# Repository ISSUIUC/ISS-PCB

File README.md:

# Welcome to the ISS-PCB repo! 🖥️⚙️⚡

# Repository Overview

* Boards: Contains all of the present boards the team is working on
    - Moved Board Archive to the [Archive](https://github.com/ISSUIUC/ISS-PCB-Archive) repo... check it out! 😁
* Docs: Contains various documents pertaining to PCB designs
* Libs: Contains various templates, symbols and footprints that we use when designing PCBs
* Scripts: Contains various codes used in PCB development
* Documentation & Tutorial Mark Down Files: 
    - README.md: Introduces the ISS-PCB Repo and pertinent information to become an amazing E-Hardware member
    - ISS-PCB-CONVENTIONS.md: Sets conventions to be followed when desiging for the ISS-PCB KiCad repo
    - HOW-TO.md: Presents brief and thorough lessons on important KiCad tools, documenation procedures, and design processes
    - GITHUB.md: An introduction to GitHub and how to use it for KiCad
    - CONTRIBUTING.md: Showcases how to setup KiCad and contribute proper work to E-Hardware. Additionally, introduces many conventions of ISS-PCB folder. 

When you commit changes to the repository, they will generally be found in the Boards folder. 

# E-Hardware PCB Documentation 

* You can find documentation about all of our PCBs in the [Spaceshot Members Box Folder](https://uofi.app.box.com/folder/273741222408). 
    - Alternatively, [Members] Spaceshot > Avionics > Development 

# How to contribute:
There are many ways to contribute to the PCBs that we build for the rocket and its accompanying systems. The timeline for building a PCB is usually as follows: 

* Formulate the requirements of the board
* Research different chips, understand their functionalities, and determine if we can use it for our purposes
* Build the board schematic using the datasheets of different chips 
* Route the board 
* Once the board is manufactured, solder all the components onto the board
* Debug the board 
* Document the board (this should be done throughout the process as well) 

Every part of constructing a PCB is hands-on, and there are lots of ways to get involved. 

To have your changes reflected on the board, it is important to commit your changes to the Github repository. To learn how to commit changes, check out the [Contributing Guide](/CONTRIBUTING.md).

# Useful Links:
Here are some links you may find useful as you are building PCBs: 

* [KiCad](https://www.kicad.org/) - software used for designing PCBs 

* [KiCad Library Conventions](https://klc.kicad.org/) - guidelines for creation of symbols, footprints, and 3D models in KiCad

* [DigiKey](https://www.digikey.com/) - used for looking up various electronic components

* [Mouser](https://www.mouser.com/) - used for looking up various electronic components

* [JLCPCB](https://jlcpcb.com) - the PCB manufacturer we primarily use

* [JLCPCB Design Rules](https://jlcpcb.com/capabilities/Capabilities) - the design constraints JLCPCB imposes

Thanks for reading, and good luck in building PCBs! 

*See a typo? Think we left some vital information out? Make a branch and edit this file!*

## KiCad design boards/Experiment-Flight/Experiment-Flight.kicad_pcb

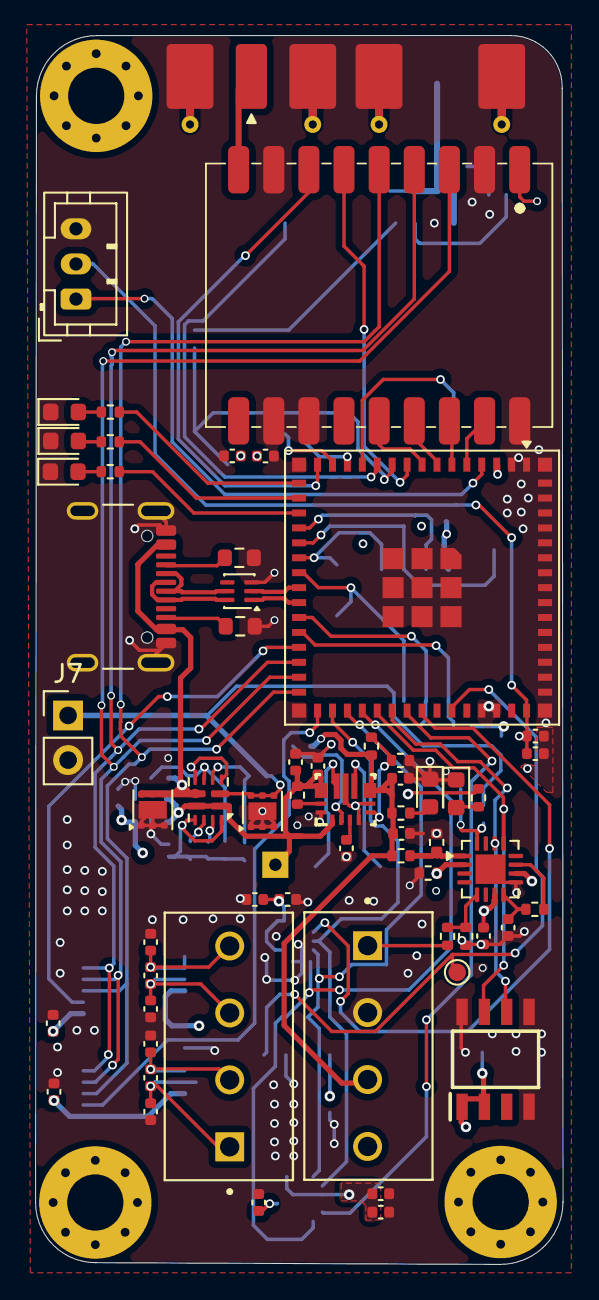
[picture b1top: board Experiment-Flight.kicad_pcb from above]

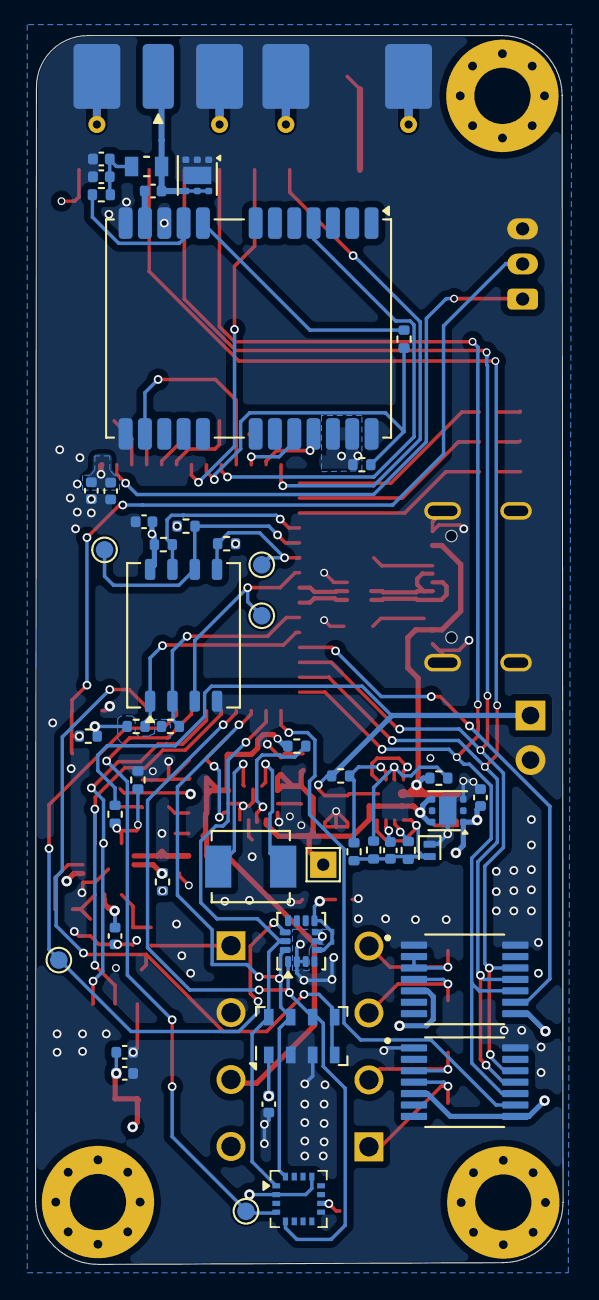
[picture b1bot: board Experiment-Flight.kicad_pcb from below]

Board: 4 copper layers, 30.0 x 70.0 mm, 113 parts (49 on the bottom side), 81 nets.

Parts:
C1, C2, C3, C5, C12, C33, C34: 1uF; C_0402_1005Metric
C6, C9, C16, C21, C23, C27: 0.1uF; C_0402_1005Metric
C8, C10: 47pF; C_0402_1005Metric
C13, C14, C18, C20, C25, C26, C28, C29, C32, C105: 100nF; C_0402_1005Metric
C15, C17, C22, C24: 0.01uF; C_0402_1005Metric
C19, C30, C36: 10uF; C_0402_1005Metric
C31, C37: 47uF; C_0402_1005Metric
C35: 4.7uF; C_0402_1005Metric
C104: 22uF; C_0402_1005Metric
D1: BAS116L; D_SOD-882
D2, D106: ORANGE_LED; LED_0603_1608Metric
D3, D104: RED LED; LED_0603_1608Metric
D105: BLUE LED; LED_0603_1608Metric
H1, H2, H3: MountingHole; MountingHole_3.2mm_M3_Pad_Via
IC1: NEO-F10N-00B; ublox_NEO
J1: USB4105-GF-A; USB_C_Receptacle_GCT_USB4105-xx-A_16P_TopMnt_Horizontal
J2, J4: SMA; SMA_Molex_73251-2120_EdgeMount_Horizontal
J5: TestPoint; TestPoint_THTPad_1.5x1.5mm_Drill0.7mm
J7: JST; PinHeader_1x02_P2.54mm_Vertical
J8: Conn_01x03; JST_PH_B3B-PH-K_1x03_P2.00mm_Vertical
J10, J11: Screw_Terminal_01x04; PHOENIX_1727036
L1: 33nH; INDC1609X100N
L2: 1uH; IND_SRP4020TA-1R0M
R1, R24, R27, R104, R105, R108, R109, R110, R111: 100k; R_0402_1005Metric
R2, R3: 5.1k; R_0603_1608Metric
R4: 20k; R_0402_1005Metric
R6: 10; R_0402_1005Metric
R7: 33; R_0402_1005Metric
R8, R16, R19: 10k; R_0402_1005Metric
R10, R11, R12, R13, R14: 50k; R_0402_1005Metric
R15: 4.7k; R_0402_1005Metric
R17, R20: 16.9k; R_0402_1005Metric
R18, R21: 5k; R_0402_1005Metric
R22: 21.5k; R_0402_1005Metric
R23: 523k; R_0402_1005Metric
R25, R26, R121, R122, R123: 470; R_0402_1005Metric
TP102, TP103, TP104, TP105, TP106, TP107: TestPoint_Small; TestPoint_Pad_D1.0mm
U1: ADS7138-Q1; WQFN-16-1EP_3x3mm_P0.5mm_EP1.68x1.68mm
U2: ESP32-S3-MINI-1U; ESP32-S2-MINI-1U
U3: ECMF02-2AMX6; ST_UQFN-6L_1.5x1.7mm_P0.5mm
U4, U13, U14: TVS1800DRV; WSON-6-1EP_2x2mm_P0.65mm_EP1x1.6mm
U5: LR2021
U6: ZDSD64GLGEAG-R; LGA-8_8x6.2mm_P1.27mm
U7: MMC5983MA; LGA-16_3x3mm_P0.5mm
U8, U9: MAX31856MUD_T; MAX31856
U10: LSM6DSV320X; LGA-14_3x2.5mm_P0.5mm_LayoutBorder3x4y
U11: MS5611-01BA; LGA-8_3x5mm_P1.25mm
U12: AS5600-ASOM; SOIC127P600X175-8N
U15: TPS63070; RNM0015A
U16: TPS2121; Texas_VQFN-HR-12_2x2.5mm_P0.5mm
U17: TPS746-Q1; WSON-6-1EP_2x2mm_P0.65mm_EP1x1.6mm

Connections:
+3V3: C2.1, C3.1, C12.1, C13.1, C14.2, C18.1, C20.1, C21.1, C25.1, C26.1, C27.1, C28.1, C29.1, C30.1, C35.1, C104.1, C105.1, IC1.22 (V_BCKP), IC1.23 (VCC), R4.1, R8.1, R10.2, R11.2, R12.2, R13.2, R14.2, R26.1, R110.1, U1.7 (AVDD), U1.10 (DVDD), U2.3 (3V3), U5.1 (VCC), U6.8 (VDD), U7.2 (VDD), U7.13 (VDDIO), U8.5 (AVDD), U8.8 (DVDD), U9.5 (AVDD), U9.8 (DVDD), U10.5 (VDDIO), U10.8 (VDD), U11.1 (VDD), U12.1 (VDD5V), U12.2 (VDD3V3), U17.1 (OUT)
/3V3_SENSE: R110.2, R111.1, U1.2 (AIN3/GPIO3)
/5V: C36.1, C37.1, J11.3, R23.1, R25.1, R27.1, R108.1, U15.7 (VOUT), U15.8 (VOUT)
/5V_SENSE: R108.2, R109.1, U1.1 (ANI2/GPIO2)
/BOOT_SW: J8.1, U2.4 (IO0)
/B_UART_RX: IC1.20 (TXD), U2.13 (IO9)
/B_UART_TX: IC1.21 (RXD), U2.14 (IO10)
/D+: J1.A6 (D+), J1.B6 (D+), U3.6 (D+_out)
/D-: J1.A7 (D-), J1.B7 (D-), U3.5 (D-_out)
/EN: C5.2, C9.1, J8.2, R4.2, U2.45 (EN)
/FLASH_CLK: TP106.1 (1_1), U2.22 (IO18), U6.3 (CLK)
/FLASH_CMD: R14.1, TP105.1 (1_1), U2.21 (IO17), U6.5 (CMD)
/FLASH_DAT0: R10.1, TP107.1 (1_1), U2.20 (IO16), U6.6 (DAT0)
/FLASH_DAT1: R11.1, U2.19 (IO15), U6.7 (DAT1)
/FLASH_DAT2: R12.1, U2.26 (IO26), U6.1 (DAT2)
/FLASH_DAT3: R13.1, U2.25 (IO21), U6.2 (DAT3)
/GNSS_ANT: C10.1, IC1.11 (RF_IN)
/GNSS_EXT_INT: IC1.4 (EXTINT), U2.11 (IO7)
/I2C_SCL: U1.13 (SCL), U2.35 (IO39), U12.7 (SCL)
/I2C_SDA: U1.14 (SDA), U2.36 (IO40), U12.6 (SDA)
/LED_BLUE: R122.1, U2.18 (IO14)
/LED_ORANGE: R123.1, U2.17 (IO13)
/LED_RED: R121.1, U2.16 (IO12)
/LNA_EN: IC1.14 (LNA_EN), U2.12 (IO8)
/LR2021_ANT: J4.1 (In), U5.9 (ANT)
/LR2021_BUSY: U2.15 (IO11), U5.7 (BUSY)
/LR2021_CS: U2.9 (IO5), U5.6 (~CS)
/LR2021_GPIO7: U2.5 (IO1), U5.17 (DIO7)
/LR2021_GPIO8: U2.6 (IO2), U5.16 (DIO8)
/LR2021_GPIO9: U2.7 (IO3), U5.15 (DIO9)
/LR2021_nRST: U2.8 (IO4), U5.14 (nRST)
/LSM_CS: TP104.1 (1_1), U2.38 (IO42), U10.12 (CS)
/MAG_CS: TP102.1 (1_1), U2.37 (IO41), U7.4 (CS)
/MAX31856_CS_1: U2.31 (IO35), U9.9 (~CS)
/MAX31856_CS_2: U2.27 (IO47), U8.9 (~CS)
/MS5611_CS: TP103.1 (1_1), U2.40 (RXD0), U11.4 (CSB), U11.5 (CSB)
/N_GNSS_RESET: R7.2, R8.2, U2.10 (IO6)
/PRESSURE+: J11.1, R15.1
/PRESSURE_SENSE: R15.2, R16.1, U1.5 (AIN6/GPIO6)
/Power/PMUX_GND: C33.1, D1.2 (A), R18.2, R21.2, R22.1, U16.3 (CP2), U16.6 (PR1), U16.9 (ST), U16.12 (GND)
/Power/SYS_POWER: C31.1, C34.1, J5.1 (Pin_1_1), R19.2, U15.1 (PS_SYNC), U15.12 (VIN), U15.13 (VIN), U16.1 (OUT), U16.8 (OUT), U17.4 (EN), U17.6 (IN)
/SPI1_MISO: U2.34 (IO38), U7.5 (SDO), U10.1 (SDO/TA0), U11.6 (SDO)
/SPI1_MOSI: U2.33 (IO37), U7.16 (SDI), U10.14 (SDA), U11.7 (SDI/SDA)
/SPI1_SCK: U2.32 (IO36), U7.1 (SCK), U10.13 (SCL), U11.8 (SCLK)
/SPI2_MISO: U2.29 (IO34), U5.3 (MISO), U8.11 (SDO), U9.11 (SDO)
/SPI2_MOSI: U2.28 (IO33), U5.4 (MOSI), U8.12 (SDI), U9.12 (SDI)
/SPI2_SCK: U2.30 (IO48), U5.5 (SCK), U8.10 (SCK), U9.10 (SCK)
/T_1+: C22.1, C23.1, J10.1, U9.4 (T+)
/T_1-: C23.2, C24.1, J10.2, U9.2 (BIAS), U9.3 (T-)
/T_2+: C15.1, C16.1, J10.3, U8.4 (T+)
/T_2-: C16.2, C17.1, J10.4, U8.2 (BIAS), U8.3 (T-)
/USB_D+: U2.24 (USB_D+), U3.1 (D+_in)
/USB_D-: U2.23 (USB_D-), U3.2 (D-_in)
/USB_POWER: J1.A4 (VBUS), J1.A9 (VBUS), J1.B4 (VBUS), J1.B9 (VBUS), R17.1, U13.4 (IN), U13.5 (IN), U13.6 (IN), U16.7 (IN1)
/VBAT: J7.1, R20.1, R104.1, U14.4 (IN), U14.5 (IN), U14.6 (IN), U16.2 (IN2)
/VBAT_SENSE: R104.2, R105.1, U1.16 (AIN1/GPIO1)
/VCC_RF: IC1.9 (VCC_RF), R6.2
GND: C1.2, C2.2, C3.2, C5.1, C6.2, C8.2, C9.2, C12.2, C13.2, C14.1, C15.2, C17.2, C18.2, C19.2, C20.2, C21.2, C22.2, C24.2, C25.2, C26.2, C27.2, C28.2, C29.2, C30.2, C31.2, C32.2, C34.2, C35.2, C36.2, C37.2, C104.2, C105.2, D1.1 (K), D2.1 (K), D3.1 (K), D104.1 (K), D105.1 (K), D106.1 (K), IC1.10 (GND_1), IC1.12 (GND_2), IC1.13 (GND_3), IC1.24 (GND_4), J1.A1 (GND), J1.A12 (GND), J1.B1 (GND), J1.B12 (GND), J1.S1 (SHIELD), J2.2 (Ext), J4.2 (Ext), J7.2, J8.3, J11.2, R2.1, R3.1, R16.2, R24.2, R105.2, R109.2, R111.2, U1.9 (GND), U1.17 (EPAD), U2.1 (GND), U2.2 (GND), U2.42 (GND), U2.43 (GND), U2.46 (GND), U2.47 (GND), U2.48 (GND), U2.49 (GND), U2.50 (GND), U2.51 (GND), U2.52 (GND), U2.53 (GND), U2.54 (GND), U2.55 (GND), U2.56 (GND), U2.57 (GND), U2.58 (GND), U2.59 (GND), U2.60 (GND), U2.61 (GND), U2.62 (GND), U2.63 (GND), U2.64 (GND), U2.65 (GND), U3.3 (GND), U4.1 (GND), U4.2 (GND), U4.3 (GND), U4.7 (GND), U5.2 (GND), U5.8 (GND), U5.11 (GND), U5.12 (GND), U5.18 (GND), U6.4 (GND), U7.9 (GND), U7.11 (GND), U8.1 (AGND), U8.14 (DGND), U9.1 (AGND), U9.14 (DGND), U10.2 (SDx), U10.3 (SCx), U10.6 (GND), U10.7 (GND), U11.2 (PS), U11.3 (GND), U12.4 (GND), U12.5 (PGO), U12.8 (DIR), U13.1 (GND), U13.2 (GND), U13.3 (GND), U13.7 (GND), U14.1 (GND), U14.2 (GND), U14.3 (GND), U14.7 (GND), U15.4 (GND), U15.6 (FB2), U15.10 (PGND), U15.15 (VSEL), U17.3 (GND), U17.7 (EP)
unnamed: C6.1, C8.1, L1.1, R6.1
unnamed: D2.2 (A), R25.2
unnamed: D3.2 (A), R26.2
unnamed: D104.2 (A), R121.2
unnamed: D105.2 (A), R122.2
unnamed: D106.2 (A), R123.2
unnamed: IC1.8 (RESET_N), R7.1
unnamed: J1.A5 (CC1), R2.2
unnamed: J1.B5 (CC2), R3.2
unnamed: C10.2, J2.1 (In), L1.2, U4.4 (IN), U4.5 (IN), U4.6 (IN)
unnamed: R1.1, U1.11 (ADDR)
unnamed: C1.1, R1.2, U1.8 (DECAP)
unnamed: C19.1, U7.10 (CAP)
unnamed: R19.1, U15.14 (EN)
unnamed: R23.2, R24.1, U15.5 (FB)
unnamed: L2.1, U15.11 (L1)
unnamed: L2.2, U15.9 (L2)
unnamed: R27.2, U15.2 (PG)
unnamed: C32.1, U15.3 (VAUX)
unnamed: R22.2, U16.10 (ILM)
unnamed: R17.2, R18.1, U16.5 (OV1)
unnamed: R20.2, R21.1, U16.4 (OV2)
unnamed: C33.2, U16.11 (SS)

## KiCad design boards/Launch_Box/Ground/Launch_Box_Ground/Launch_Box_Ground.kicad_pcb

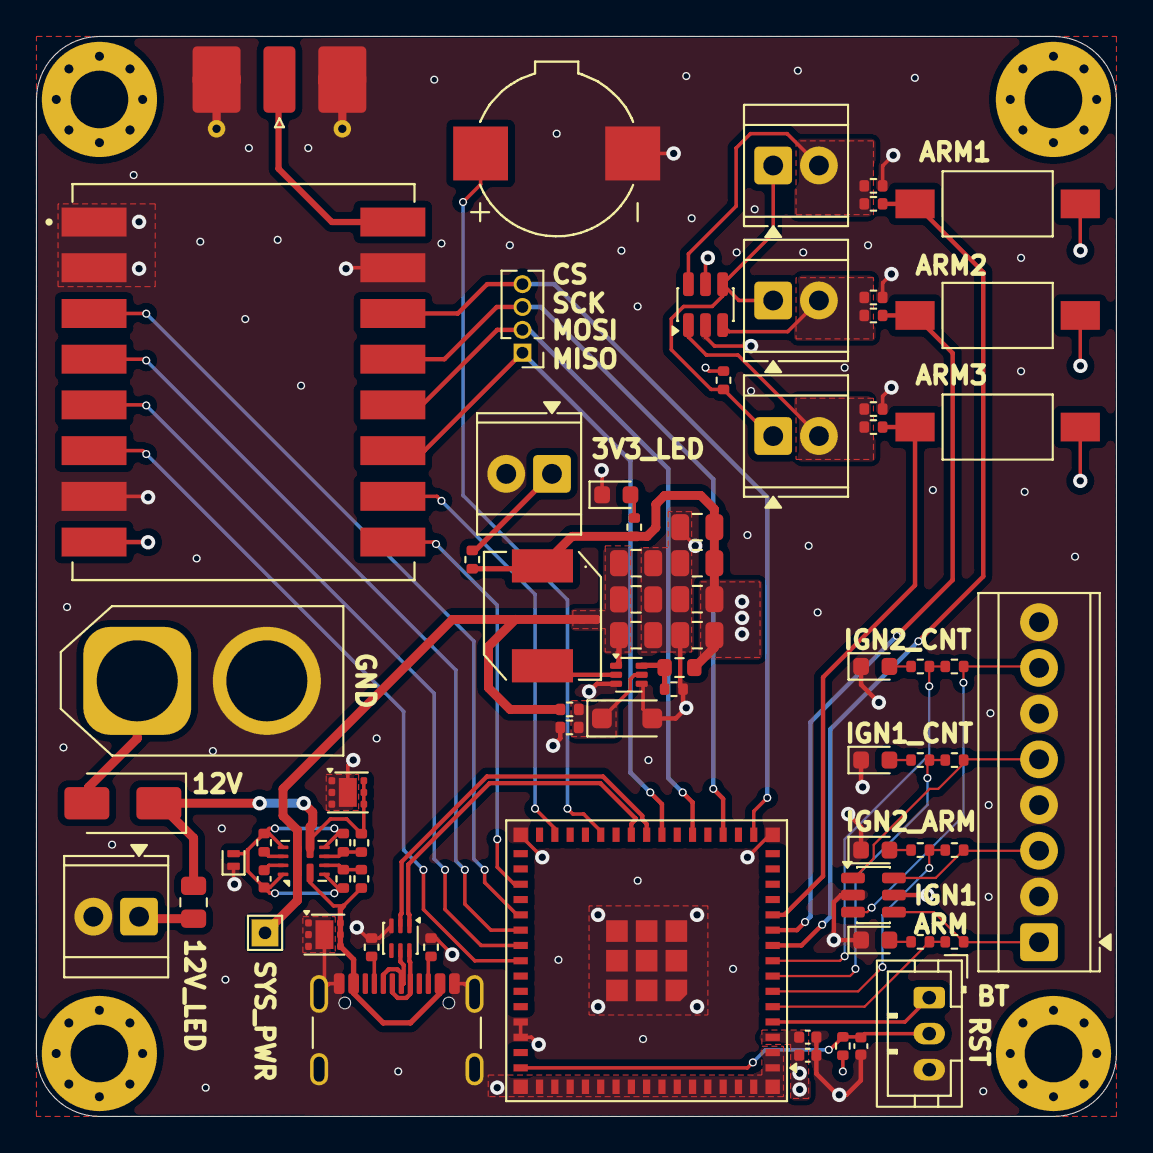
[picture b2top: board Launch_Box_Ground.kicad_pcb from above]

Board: 4 copper layers, 60.0 x 60.0 mm, 79 parts (0 on the bottom side), 56 nets.

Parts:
BZ1: Buzzer; Buzzer_SMTB-0927-TW-R
C1: 22uF; C_0402_1005Metric
C2: 100nF; C_0402_1005Metric
C3, C8: 1uF; C_0402_1005Metric
C4: 0.1uF; C_0805_2012Metric
C5, C6: 10uF; C_0805_2012Metric
C7, C9, C10, C11: 22uF; C_0805_2012Metric
D1: SS34; D_SMA
D2, D3: GREEN LED; LED_0603_1608Metric
D4, D5, D8: RED LED; LED_0603_1608Metric
D6: BZT52H-A5V1-QX; D_SOD-123F
D7: BAS116L; D_SOD-882
H1, H2, H3, H4: M3; MountingHole_3.2mm_M3_Pad_Via
J1: Conn_01x03; JST_PH_B3B-PH-K_1x03_P2.00mm_Vertical
J2: USB4105-GF-A; USB_C_Receptacle_GCT_USB4105-xx-A_16P_TopMnt_Horizontal
J3: Conn_01x04; PinHeader_1x04_P1.27mm_Vertical
J4: SMA
J5: XT60; AMASS_XT60-F_1x02_P7.20mm_Vertical
J6, J8, J9, J11, J12: Screw_Terminal_01x02; TerminalBlock_TE_282834-2_1x02_P2.54mm_Horizontal
J7: Screw_Terminal_01x08; TerminalBlock_TE_282834-8_1x08_P2.54mm_Horizontal
J10: TestPoint; TestPoint_THTPad_1.5x1.5mm_Drill0.7mm
L1: 2.2uH; L_TDK_SPM6530
R1, R21: 20k; R_0402_1005Metric
R2, R3: 5.1k; R_0402_1005Metric
R4, R5, R9, R10, R11, R12, R13, R14, R28, R30: 470; R_0402_1005Metric
R6: 100R; R_0402_1005Metric
R7, R15, R16: 1k; R_0402_1005Metric
R8, R17, R18: 10k; R_0402_1005Metric
R19: 62k; R_0402_1005Metric
R20, R24: 5k; R_0402_1005Metric
R22, R25: 30k; R_0402_1005Metric
R23: 16.9k; R_0402_1005Metric
R26: 135k; R_0603_1608Metric
R27: 80.6k; R_0402_1005Metric
R29: 2k; R_0805_2012Metric
SW1, SW2, SW3: SW_Push; SW_SPST_FSMSM
U1: ESP32-S3-MINI-1U; ESP32-S2-MINI-1U
U2: CORE1262-868M; XCVR_CORE1262-868M
U3: ECMF02-2AMX6; ST_UQFN-6L_1.5x1.7mm_P0.5mm
U4, U5: SRV05-4; SOT-23-6
U6, U7: TVS1800DRV; WSON-6-1EP_2x2mm_P0.65mm_EP1x1.6mm
U8: TI_TPS566242; SOT-563
U9: TPS2121; Texas_VQFN-HR-12_2x2.5mm_P0.5mm

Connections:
+3V3: C1.1, C2.1, C7.1, C9.1, C10.1, C11.1, L1.1, R1.2, R6.1, R26.2, R28.1, R30.1, SW1.1, SW2.1, SW3.1, U1.3 (3V3), U2.8 (3V3), U4.5 (VP), U5.5 (VP)
/12V_VBAT: D1.1 (K), R19.1, R29.1, U6.4 (IN), U6.5 (IN), U6.6 (IN), U9.7 (IN1)
/ANT_SX1262: J4.1 (In), U2.16 (ANT)
/ARMED_1: R15.1, SW1.2, U1.9 (IO5)
/ARMED_2: R16.1, SW2.2, U1.10 (IO6)
/BOOT_SW: J1.1, U1.4 (IO0)
/BUZZER: BZ1.1 (+), U1.26 (IO26)
/D+: J2.A6 (D+), J2.B6 (D+), U3.6 (D+_out)
/D-: J2.A7 (D-), J2.B7 (D-), U3.5 (D-_out)
/Ground_User_Controls/TVS_3V3_FEED: J6.1, J8.1, J9.1, R6.2, U4.4 (IO3)
/Ground_User_Controls/TVS_ARMED_1: J8.2, R15.2, R17.1, U4.6 (IO4)
/Ground_User_Controls/TVS_ARMED_2: J9.2, R16.2, R18.1, U4.3 (IO2)
/Ground_User_Controls/TVS_IGN_1_ARM: J7.1, R11.1, U5.4 (IO3)
/Ground_User_Controls/TVS_IGN_1_CNT: J7.5, R13.1, U5.1 (IO1)
/Ground_User_Controls/TVS_IGN_2_ARM: J7.3, R12.1, U5.6 (IO4)
/Ground_User_Controls/TVS_IGN_2_CNT: J7.7, R14.1, U5.3 (IO2)
/Ground_User_Controls/TVS_LAUNCH: J6.2, R7.2, R8.1, U4.1 (IO1)
/LAUNCH: R7.1, SW3.2, U1.11 (IO7)
/LED_RED_IGNITER_1_ARMED: R9.1, R11.2, U1.5 (IO1)
/LED_RED_IGNITER_1_CONTINUITY: R4.1, R13.2, U1.7 (IO3)
/LED_RED_IGNITER_2_ARMED: R10.1, R12.2, U1.6 (IO2)
/LED_RED_IGNITER_2_CONTINUITY: R5.1, R14.2, U1.8 (IO4)
/Power/PMUX_GND: C8.1, D7.2 (A), R20.2, R24.2, R27.1, U9.3 (CP2), U9.6 (PR1), U9.9 (ST), U9.12 (GND)
/Power/SYS_POWER: C4.1, C5.1, C6.1, J10.1 (Pin_1_1), R21.1, U8.1 (VIN), U9.1 (OUT), U9.8 (OUT)
/RESET_SW: C3.1, J1.2, R1.1, U1.45 (EN)
/SPI0_MISO: J3.1, U1.22 (IO18), U2.11 (MISO)
/SPI0_MOSI: J3.2, U1.20 (IO16), U2.12 (MOSI)
/SPI0_SCK: J3.3, U1.18 (IO14), U2.13 (CLK)
/SX1262_BUSY: U1.33 (IO37), U2.9 (BUSY)
/SX1262_CS: J3.4, U1.16 (IO12), U2.14 (CS)
/SX1262_GPIO_1: U1.38 (IO42), U2.6 (DIO1)
/SX1262_GPIO_2: U1.37 (IO41), U2.5 (DIO2)
/SX1262_RESET: U1.29 (IO34), U2.10 (RESET)
/SX1262_RX_EN: U1.35 (IO39), U2.3 (RXEN)
/SX1262_TX_EN: U1.36 (IO40), U2.4 (TXEN)
/USB_D+: U1.24 (USB_D+), U3.1 (D+_in)
/USB_D-: U1.23 (USB_D-), U3.2 (D-_in)
/USB_POWER: J2.A4 (VBUS), J2.A9 (VBUS), J2.B4 (VBUS), J2.B9 (VBUS), R23.1, U7.4 (IN), U7.5 (IN), U7.6 (IN), U9.2 (IN2)
GND: BZ1.2 (-), C1.2, C2.2, C3.2, C4.2, C5.2, C6.2, C7.2, C9.2, C10.2, C11.2, D2.1 (K), D3.1 (K), D4.1 (K), D5.1 (K), D6.2 (A), D7.1 (K), D8.1 (K), J1.3, J2.A1 (GND), J2.A12 (GND), J2.B1 (GND), J2.B12 (GND), J2.S1 (SHIELD), J4.2 (Ext), J5.2, J7.2, J7.4, J7.6, J7.8, J11.2, J12.2, R2.2, R3.2, R8.2, R17.2, R18.2, R22.2, R25.2, U1.1 (GND), U1.2 (GND), U1.42 (GND), U1.43 (GND), U1.46 (GND), U1.47 (GND), U1.48 (GND), U1.49 (GND), U1.50 (GND), U1.51 (GND), U1.52 (GND), U1.53 (GND), U1.54 (GND), U1.55 (GND), U1.56 (GND), U1.57 (GND), U1.58 (GND), U1.59 (GND), U1.60 (GND), U1.61 (GND), U1.62 (GND), U1.63 (GND), U1.64 (GND), U1.65 (GND), U2.1 (GND), U2.2 (GND), U2.7 (GND), U2.15 (GND), U3.3 (GND), U4.2 (VN), U5.2 (VN), U6.1 (GND), U6.2 (GND), U6.3 (GND), U6.7 (GND), U7.1 (GND), U7.2 (GND), U7.3 (GND), U7.7 (GND), U8.3 (GND), U8.4 (AGND)
unnamed: D1.2 (A), J5.1
unnamed: D2.2 (A), R4.2
unnamed: D3.2 (A), R5.2
unnamed: D4.2 (A), R9.2
unnamed: D5.2 (A), R10.2
unnamed: D6.1 (K), R21.2, R22.1, U8.5 (EN)
unnamed: D8.2 (A), R28.2
unnamed: J2.A5 (CC1), R2.1
unnamed: J2.B5 (CC2), R3.1
unnamed: J11.1, R29.2
unnamed: J12.1, R30.2
unnamed: R25.1, R26.1, U8.6 (FB)
unnamed: L1.2, U8.2 (SW)
unnamed: R27.2, U9.10 (ILM)
unnamed: R19.2, R20.1, U9.5 (OV1)
unnamed: R23.2, R24.1, U9.4 (OV2)
unnamed: C8.2, U9.11 (SS)

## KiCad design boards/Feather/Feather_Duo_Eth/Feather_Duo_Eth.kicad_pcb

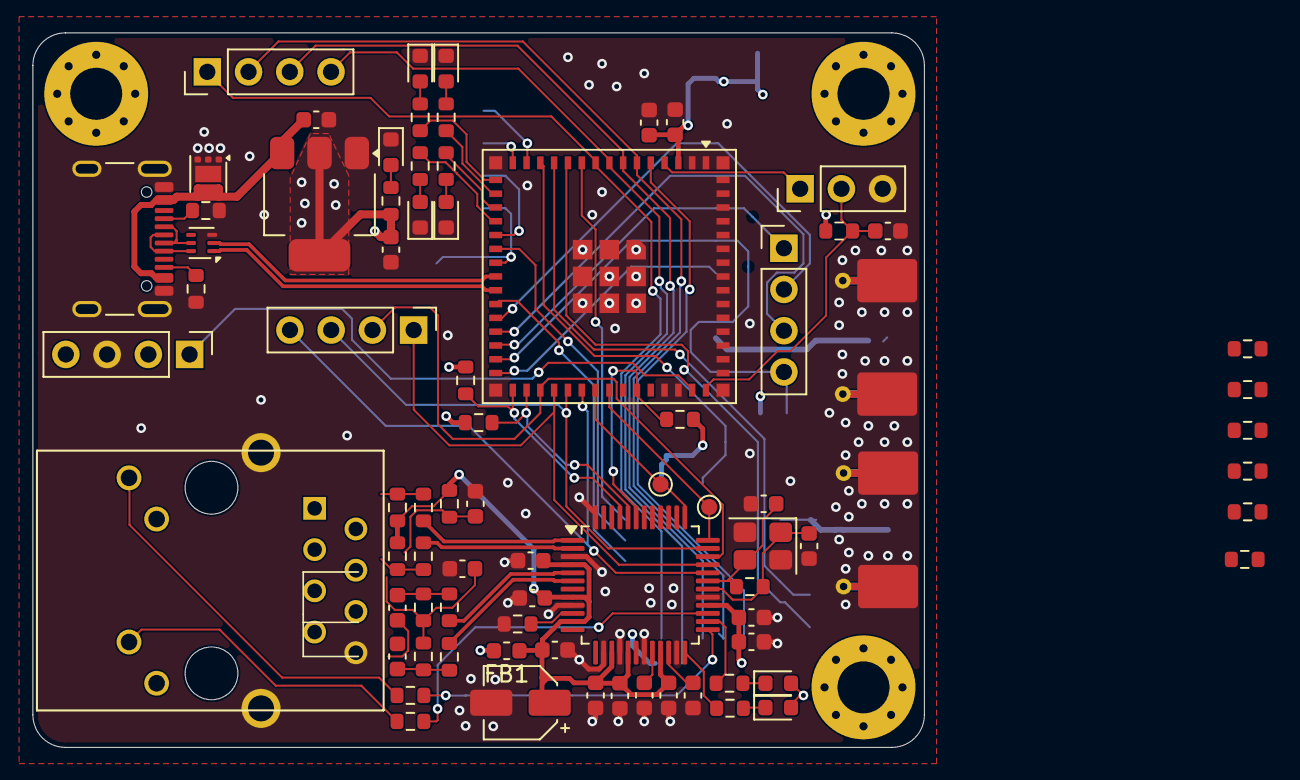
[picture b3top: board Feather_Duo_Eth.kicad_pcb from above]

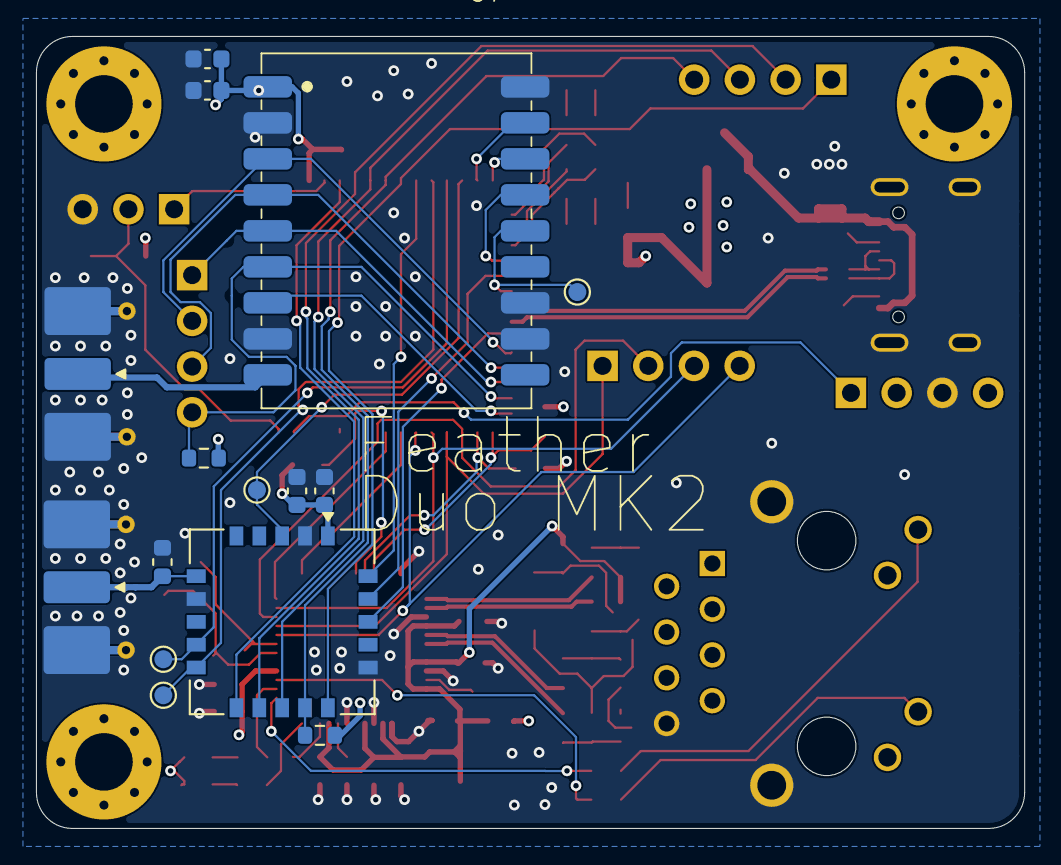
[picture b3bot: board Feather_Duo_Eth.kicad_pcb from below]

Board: 4 copper layers, 54.9 x 44.0 mm, 95 parts (15 on the bottom side), 78 nets.

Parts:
C1, C5: 22uF; C_0603_1608Metric
C2, C6, C8, C9, C12, C15, C17, C20: 0.1uF; C_0603_1608Metric
C3, C25: 1uF; C_0603_1608Metric
C4, C22, C23: 10uF; C_0603_1608Metric
C7, C10: 27pF; C_0603_1608Metric
C11: 22nF; C_0603_1608Metric
C13, C16: 6.8nF; C_0603_1608Metric
C14, C19, C24: 10nF; C_0603_1608Metric
C18: 10uF; CP_Elec_4x5.8
C21: 4.7uF; C_0603_1608Metric
C26: 100nF; C_0603_1608Metric
D1, D3, D7: RED LED; LED_0603_1608Metric
D2, D6: BLUE LED; LED_0603_1608Metric
D4: ORANGE LED; LED_0603_1608Metric
D5: GREEN LED; LED_0603_1608Metric
FB1: 120 Ohms @ 100 MHz; L_0603_1608Metric
H1, H2, H3: M3; MountingHole_3.2mm_M3_Pad_Via
J1: Conn_01x03; PinHeader_1x03_P2.54mm_Vertical
J2, J3, J4, J6: Conn_01x04; PinHeader_1x04_P2.54mm_Vertical
J5: USB4105-GF-A; USB_C_Receptacle_GCT_USB4105-xx-A_16P_TopMnt_Horizontal
J7, J8: SMA; SMA_Molex_73251-2120_EdgeMount_Horizontal
L1: 330nH; L_0603_1608Metric
P1: J1B1211CCD
R1: 20k; R_0603_1608Metric
R2, R3, R4, R5, R6, R7, R10: 470; R_0603_1608Metric
R8, R9: 5.1k; R_0603_1608Metric
R11, R16, R19: 10k; R_0603_1608Metric
R12, R13, R14, R15: 33R; R_0603_1608Metric
R17, R20, R22, R23: 49.9R; R_0603_1608Metric
R18: 1M; R_0603_1608Metric
R21: 10R; R_0603_1608Metric
R24, R25: 220R; R_0603_1608Metric
R26: 12.4k; R_0603_1608Metric
R27, R28: 100k; R_0603_1608Metric
R29, R30, R31, R32, R33, R34: 0R; R_0603_1608Metric
TP1, TP2, TP3, TP4, TP5, TP6: TestPoint; TestPoint_Pad_D1.0mm
U1: ESP32-S3-MINI-1U; ESP32-S2-MINI-1U
U2: ECMF02-2AMX6; ST_UQFN-6L_1.5x1.7mm_P0.5mm
U3: TVS1800DRV; WSON-6-1EP_2x2mm_P0.65mm_EP1x1.6mm
U4: AMS1117-3.3; SOT-223-3_TabPin2
U5: W5500; LQFP-48_7x7mm_P0.5mm
U6: E22-400MM22S
U7: LR2021
Y1: 25MHz; Crystal_SMD_TXC_7M-4Pin_3.2x2.5mm

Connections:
+3V3: C1.2, C2.2, C5.1, C20.1, C22.1, C23.1, C24.1, C25.1, C26.1, D1.2 (A), D2.2 (A), FB1.2, J6.4, P1.10 (GRN+), P1.12 (YLW+), R1.1, R10.1, R11.1, R16.1, R19.1, R27.1, R28.1, U1.3 (3V3), U4.2 (VO), U5.28 (VDD), U6.1 (VCC), U7.1 (VCC)
+3V3A: C6.1, C8.1, C9.1, C12.1, C15.1, C17.1, C18.1, FB1.1, R17.1, R20.1, R21.1, U5.4 (AVDD), U5.8 (AVDD), U5.11 (AVDD), U5.15 (AVDD), U5.17 (AVDD), U5.21 (AVDD)
+5V: C4.1, J5.A4 (VBUS), J5.A9 (VBUS), J5.B4 (VBUS), J5.B9 (VBUS), U3.4 (IN), U3.5 (IN), U3.6 (IN), U4.3 (VI)
/ACT_LED: P1.11 (YLW-), R25.2
/BOOT: J1.1, U1.4 (IO0)
/D+: J5.A6 (D+), J5.B6 (D+), U2.6 (D+_out)
/D-: J5.A7 (D-), J5.B7 (D-), U2.5 (D-_out)
/DUPLED: R7.2, U5.26 (DUPLED)
/E22_BUSY: U1.5 (IO1), U6.11 (BUSY)
/E22_CS: J2.4, R27.2, U1.8 (IO4), U6.14 (NSS)
/E22_DI01: U1.10 (IO6), U6.20 (DIO1)
/E22_DI02: U1.21 (IO17), U6.19 (DIO2)
/E22_DI03: U1.25 (IO21), U6.18 (DIO3)
/E22_MISO: J2.2, R30.2, U1.6 (IO2), U6.12 (MISO)
/E22_MOSI: J2.3, R31.2, U1.7 (IO3), U6.13 (MOSI)
/E22_RESET: TP4.1 (1_1), U1.13 (IO9), U6.3 (NRST)
/E22_RXEN: TP5.1 (1_1), U1.11 (IO7), U6.10 (RXEN)
/E22_SCK: J2.1, R29.2, U1.9 (IO5), U6.15 (SCK)
/E22_TXEN: TP6.1 (1_1), U1.12 (IO8), U6.9 (TXEN)
/IO46: J6.1, U1.44 (IO46)
/LED_BLUE: R5.1, U1.16 (IO12)
/LED_GREEN: R4.1, U1.17 (IO13)
/LED_ORANGE: R3.1, U1.18 (IO14)
/LED_RED: R2.1, U1.19 (IO15)
/LINK_LED: P1.9 (GRN-), R24.2
/LR2021_BUSY: U1.30 (IO48), U7.7 (BUSY)
/LR2021_CS: J3.4, R28.2, U1.29 (IO34), U7.6 (~CS)
/LR2021_GPIO7: U1.14 (IO10), U7.17 (DIO7)
/LR2021_GPIO8: U1.15 (IO11), U7.16 (DIO8)
/LR2021_GPIO9: U1.20 (IO16), U7.15 (DIO9)
/LR2021_MISO: J3.2, R33.2, U1.26 (IO26), U7.3 (MISO)
/LR2021_MOSI: J3.3, R34.2, U1.27 (IO47), U7.4 (MOSI)
/LR2021_SCK: J3.1, R32.2, U1.28 (IO33), U7.5 (SCK)
/LR2021_nRST: TP3.1 (1_1), U1.22 (IO18), U7.14 (nRST)
/PMODE0: R11.2, U1.31 (IO35), U5.45 (PMODE0)
/PMODE1: R16.2, U1.32 (IO36), U5.44 (PMODE1)
/PMODE2: R19.2, U1.40 (RXD0), U5.43 (PMODE2)
/RESET: C3.1, J1.2, R1.2, U1.45 (EN)
/RXN: R15.1, U5.5 (RXN)
/RXP: R14.1, U5.6 (RXP)
/SPDLED: R6.2, U5.24 (SPDLED)
/TXN: R13.1, U5.1 (TXN)
/TXP: R12.1, U5.2 (TXP)
/USB_D+: U1.24 (IO20), U2.1 (D+_in)
/USB_D-: U1.23 (IO19), U2.2 (D-_in)
/W5500_CS: J4.4, U1.36 (IO40), U5.32 (~SCS)
/W5500_INT: TP1.1 (1_1), U1.38 (IO42), U5.36 (~INT)
/W5500_MISO: J4.2, R30.1, R33.1, U1.33 (IO37), U5.34 (MISO)
/W5500_MOSI: J4.3, R31.1, R34.1, U1.35 (IO39), U5.35 (MOSI)
/W5500_RESET: TP2.1 (1_1), U1.37 (IO41), U5.37 (~RST)
/W5500_SCK: J4.1, R29.1, R32.1, U1.34 (IO38), U5.33 (SCLK)
GND: C1.1, C2.1, C3.2, C4.2, C5.2, C6.2, C7.2, C8.2, C9.2, C10.2, C11.2, C12.2, C14.2, C15.2, C17.2, C18.2, C19.2, C20.2, C21.2, C22.2, C23.2, C24.2, C25.2, C26.2, D3.1 (K), D4.1 (K), D5.1 (K), D6.1 (K), D7.1 (K), J1.3, J5.A1 (GND), J5.A12 (GND), J5.B1 (GND), J5.B12 (GND), J5.S1 (SHIELD), J6.3, J7.2 (Ext), J8.2 (Ext), L1.2, P1.8 (GH_GND@1), P1.13 (CH_GND@2), P1.14 (CH_GND@3), R8.2, R9.2, R26.2, U1.1 (GND), U1.2 (GND), U1.42 (GND), U1.43 (GND), U1.46 (GND), U1.47 (GND), U1.48 (GND), U1.49 (GND), U1.50 (GND), U1.51 (GND), U1.52 (GND), U1.53 (GND), U1.54 (GND), U1.55 (GND), U1.56 (GND), U1.57 (GND), U1.58 (GND), U1.59 (GND), U1.60 (GND), U1.61 (GND), U1.62 (GND), U1.63 (GND), U1.64 (GND), U1.65 (GND), U2.3 (GND), U3.1 (GND), U3.2 (GND), U3.3 (GND), U3.7 (GND), U4.1 (GND), U5.3 (AGND), U5.9 (AGND), U5.14 (AGND), U5.16 (AGND), U5.19 (AGND), U5.23 (RSVD), U5.29 (GND), U5.48 (AGND), U6.2 (GND), U6.7 (GND), U6.16 (GND), U7.2 (GND), U7.8 (GND), U7.11 (GND), U7.12 (GND), U7.18 (GND), Y1.2 (G), Y1.4 (G)
unnamed: C13.1, R14.2, R22.1
unnamed: C16.1, R15.2, R23.1
unnamed: D1.1 (K), R6.1
unnamed: D2.1 (K), R7.1
unnamed: D3.2 (A), R2.2
unnamed: D4.2 (A), R3.2
unnamed: D5.2 (A), R4.2
unnamed: D6.2 (A), R5.2
unnamed: D7.2 (A), R10.2
unnamed: J5.A5 (CC1), R8.1
unnamed: J5.B5 (CC2), R9.1
unnamed: J7.1 (In), L1.1, U6.6 (ANT)
unnamed: J8.1 (In), U7.9 (ANT)
unnamed: C14.1, P1.5 (RCT), R22.2, R23.2
unnamed: C13.2, P1.4 (RD+)
unnamed: C16.2, P1.6 (RD-)
unnamed: C11.1, P1.2 (TCT), R21.2
unnamed: P1.1 (TD+), R12.2, R17.2
unnamed: P1.3 (TD-), R13.2, R20.2
unnamed: C19.1, U5.22 (1V2O)
unnamed: R25.1, U5.27 (ACTLED)
unnamed: R26.1, U5.10 (EXRES1)
unnamed: R24.1, U5.25 (LINKLED)
unnamed: C21.1, U5.20 (TOCAP)
unnamed: C7.1, R18.1, U5.30 (XI/CLKIN), Y1.1
unnamed: C10.1, R18.2, U5.31 (XO), Y1.3

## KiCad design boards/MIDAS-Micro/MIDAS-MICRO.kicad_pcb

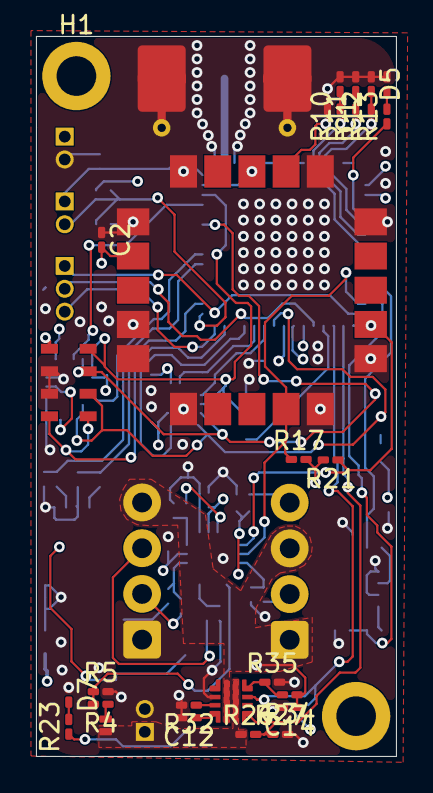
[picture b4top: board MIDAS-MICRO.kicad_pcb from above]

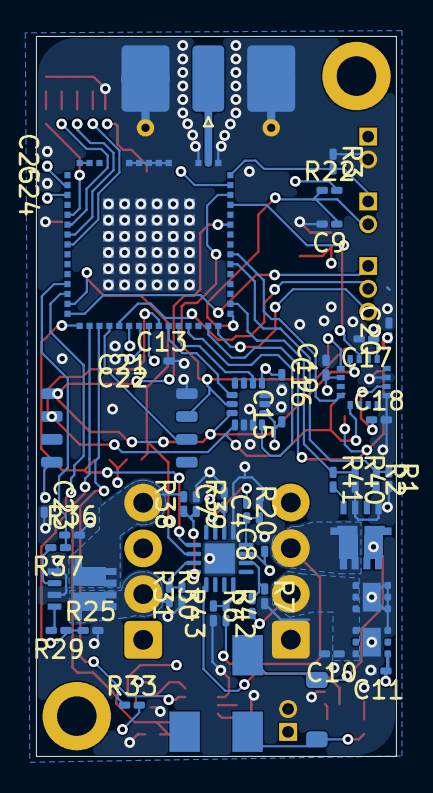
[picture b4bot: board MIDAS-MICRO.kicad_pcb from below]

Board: 4 copper layers, 20.0 x 40.0 mm, 85 parts (50 on the bottom side), 60 nets.

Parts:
C1, C2, C13, C15, C16, C17, C19, C20, C21, C22, C23, C24, C25: 100nF; C_0201_0603Metric_Pad0.64x0.40mm_HandSolder
C4, C7, C8, C9, C10: 1uF; C_0201_0603Metric_Pad0.64x0.40mm_HandSolder
C11, C14: 4.7uF; C_0201_0603Metric_Pad0.64x0.40mm_HandSolder
C12: 4.7nF; C_0201_0603Metric_Pad0.64x0.40mm_HandSolder
C18: 10uF; C_0201_0603Metric_Pad0.64x0.40mm_HandSolder
D1: 1N4148W; D_SOD-123
D2: SDM05U40CSP; D_SOD-882
D3: RED LED; LED_0201_0603Metric_Pad0.64x0.40mm_HandSolder
D4: ORANGE LED; LED_0201_0603Metric_Pad0.64x0.40mm_HandSolder
D5: GREEN LED; L_0201_0603Metric_Pad0.64x0.40mm_HandSolder
D6: BLUE LED; LED_0201_0603Metric_Pad0.64x0.40mm_HandSolder
D7: RED LED; L_0201_0603Metric_Pad0.64x0.40mm_HandSolder
H1, H2: M2; MountingHole_2.2mm_M2_DIN965_Pad
J1, J2, J3: Conn_01x02; PinHeader_1x02_P1.27mm_Vertical
J4: Conn_01x03; PinHeader_1x03_P1.27mm_Vertical
J5: SMA; SMA_Molex_73251-2120_EdgeMount_Horizontal
J6, J7: Screw_Terminal_01x04; TerminalBlock_TE_282834-4_1x04_P2.54mm_Horizontal
LS1: SMT-0540-T-9-R; XDCR_SMT-0540-T-9-R
Q1, Q2: Si7232DN; Vishay_PowerPAK_1212-8_Dual
R1, R25, R36, R40: 3.3k; R_0201_0603Metric_Pad0.64x0.40mm_HandSolder
R2, R29, R33, R37, R41: 1k; R_0201_0603Metric_Pad0.64x0.40mm_HandSolder
R3, R17, R21: 10k; R_0201_0603Metric_Pad0.64x0.40mm_HandSolder
R4: 560k; R_0201_0603Metric_Pad0.64x0.40mm_HandSolder
R5, R6, R7, R20, R27, R30, R35, R38, R42: 100k; R_0201_0603Metric_Pad0.64x0.40mm_HandSolder
R10, R11, R12, R13, R23: 470; R_0201_0603Metric_Pad0.64x0.40mm_HandSolder
R22: 20k; R_0201_0603Metric_Pad0.64x0.40mm_HandSolder
R26, R34: 150k; R_0201_0603Metric_Pad0.64x0.40mm_HandSolder
R31, R39, R43: 18k; R_0201_0603Metric_Pad0.64x0.40mm_HandSolder
R32: 820; R_0201_0603Metric_Pad0.64x0.40mm_HandSolder
U1: SAM-M10Q; ublox_SAM-M8Q
U2: STM32WL5MOCH6STR; STM32WL5MOC
U5: ADS7138-Q1; WQFN-16-1EP_3x3mm_P0.5mm_EP1.68x1.68mm
U6: XTSD04G; LGA-8_8x6.2mm_P1.27mm
U7: TVS1800DRV; WSON-6-1EP_2x2mm_P0.65mm_EP1x1.6mm
U8: TPS746-Q1; WSON-6-1EP_2x2mm_P0.65mm_EP1x1.6mm
U10: TPS25947; VQFN-HR-RPW0010A
U11: LSM6DSV320X; LGA-14_3x2.5mm_P0.5mm_LayoutBorder3x4y
U12: MMC5983MA; LGA-16_3x3mm_P0.5mm
U13: MS5611-01BA; LGA-8_3x5mm_P1.25mm

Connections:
+3V3: C1.2, C2.2, C7.1, C8.1, C11.1, C13.1, C15.1, C16.1, C17.1, C19.1, C20.1, C21.1, C22.1, C23.1, C24.1, C25.1, D1.1 (K), J2.1, LS1.LOAD+, R17.2, R21.2, R22.2, R23.1, R33.2, U1.2 (VCC_IO), U1.17 (VCC), U2.28 (VDD), U2.29 (VDDPA), U2.47 (VBAT_M), U2.48 (VREF+), U2.49 (VDDA), U5.7 (AVDD), U5.10 (DVDD), U6.8 (VDD), U8.1 (OUT), U11.5 (VDDIO), U11.8 (VDD), U12.2 (VDD), U12.13 (VDDIO), U13.1 (VDD)
/ANT: J5.1 (In), U2.17 (ANT)
/BOOT_SW: J3.1, R3.2, U2.15 (PH3-BOOT0)
/BUZZER: R1.1, R2.1, U2.6 (PA1)
/FIRE_A: R25.1, R29.1, U2.39 (PA10)
/FIRE_B: R36.1, R37.1, U2.38 (PC13)
/FIRE_C: R40.1, R41.1, U2.2 (PC0)
/FLASH_CS: U2.45 (PB15), U6.2 (SD3/~CS)
/I2C_SCL: R21.1, U1.12 (SCL), U2.42 (PA12), U5.13 (SCL)
/I2C_SDA: R17.1, U1.9 (SDA), U2.40 (PA11), U5.14 (SDA)
/JTCK/SWCLK: J4.2, U2.46 (PA14)
/JTDO: J4.3, U2.56 (PB3)
/JTMS/SWDIO: J4.1, U2.41 (PA13)
/LED_BLUE: R13.1, U2.31 (PA9)
/LED_GREEN: R12.1, U2.32 (PB12)
/LED_ORANGE: R11.1, U2.33 (PB1)
/LED_RED: R10.1, U2.34 (PA0)
/LSM_CS: U2.51 (PA15), U11.12 (CS)
/LSM_INT1: U2.53 (PB8), U11.4 (INT1)
/LSM_INT2: U2.52 (PB7), U11.9 (INT2)
/MAG_CS: U2.7 (PB11), U12.4 (CS)
/MAG_INT: U2.12 (PA4), U12.15 (INT)
/MS5611_CS: U2.55 (PB5), U13.4 (CSB), U13.5 (CSB)
/NRST: C9.1, J3.2, R22.1, U2.1 (NRST)
/PYRO_A: J6.2, Q2.5 (D2), R30.2
/PYRO_B: J6.4, Q2.6 (D1), R38.2
/PYRO_C: J7.3, Q1.5 (D2), R42.2
/PYRO_EN: R26.2, R27.1, U2.43 (PC2), U10.1 (EN/UVLO)
/PYRO_PG: R33.1, U2.44 (PB9), U10.3 (PG/AUXOFF)
/PYRO_SENSE: R4.2, R5.1, U5.1 (ANI2/GPIO2)
/Pyro/PGTH: R34.2, R35.1, U10.4 (PGTH/NFLT)
/SAM_RESET: U1.18 (~RESET), U2.14 (PA8)
/SENSE_A: R30.1, R31.2, U5.15 (AIN0/GPIO0)
/SENSE_B: R38.1, R39.2, U5.16 (AIN1/GPIO1)
/SENSE_C: R42.1, R43.2, U5.4 (AIN5/GPIO5)
/SPI1_MISO: U2.50 (PA6), U6.6 (SD0/DO), U11.1 (SDO/TA0), U12.5 (SDO), U13.6 (SDO)
/SPI1_MOSI: U2.10 (PA7), U6.5 (CMD/DI), U11.14 (SDA), U12.16 (SDI), U13.7 (SDI/SDA)
/SPI1_SCK: U2.13 (PA5), U6.3 (CLK), U11.13 (SCL), U12.1 (SCK), U13.8 (SCLK)
/VBAT: C10.1, J7.2, R6.1, U7.4 (IN), U7.5 (IN), U7.6 (IN), U8.4 (EN), U8.6 (IN)
/VBAT_PYRO: D2.2 (A), J1.1, R26.1, U10.5 (IN)
/VBAT_SENSE: R6.2, R7.1, U5.6 (AIN7/GPIO7)
/V_PYRO: C14.1, J6.1, J6.3, J7.4, R34.1, U10.6 (OUT)
GND: C1.1, C2.1, C4.2, C7.2, C8.2, C9.2, C10.2, C11.2, C12.2, C13.2, C14.2, C15.2, C16.2, C17.2, C18.2, C19.2, C20.2, C21.2, C22.2, C23.2, C24.2, C25.2, D3.1 (K), D4.1 (K), D5.1 (K), D6.1 (K), D7.1 (K), J1.2, J2.2, J5.2 (Ext), J7.1, Q1.1 (S1), Q1.3 (S2), Q2.1 (S1), Q2.3 (S2), R1.2, R3.1, R5.2, R7.2, R25.2, R27.2, R31.1, R32.2, R35.2, R36.2, R39.1, R40.2, R43.1, U1.1 (GND), U1.4 (GND), U1.5 (GND), U1.6 (GND), U1.10 (GND), U1.11 (GND), U1.15 (GND), U1.16 (GND), U1.20 (GND), U2.16 (VSSRF), U2.18 (VSSRF), U2.19 (VSS), U2.20 (VSS), U2.21 (VSS), U2.22 (VSS), U2.23 (VSS), U2.57 (VSS), U2.58 (VSS), U2.59 (VSS), U2.60 (VSS), U2.61 (VSS), U2.62 (VSS), U2.63 (VSS), U2.64 (VSS), U2.65 (VSS), U2.66 (VSS), U2.67 (VSS), U2.68 (VSS), U2.69 (VSS), U2.70 (VSS), U2.71 (VSS), U2.72 (VSS), U2.73 (VSS), U2.74 (VSS), U2.75 (VSS), U2.76 (VSS), U2.77 (VSS), U2.78 (VSS), U2.79 (VSS), U2.80 (VSS), U2.81 (VSS), U2.82 (VSS), U2.83 (VSS), U2.84 (VSS), U2.85 (VSS), U2.86 (VSS), U2.87 (VSS), U2.88 (VSS), U2.89 (VSS), U2.90 (VSS), U2.91 (VSS), U2.92 (VSS), U5.9 (GND), U5.17 (EPAD), U6.4 (VSS), U7.1 (GND), U7.2 (GND), U7.3 (GND), U7.7 (GND), U8.3 (GND), U8.7 (EP), U10.8 (GND), U11.2 (SDx), U11.3 (SCx), U11.6 (GND), U11.7 (GND), U12.9 (GND), U12.11 (GND), U13.2 (PS), U13.3 (GND)
unnamed: D1.2 (A), LS1.LOAD-, Q1.6 (D1)
unnamed: D2.1 (K), R4.1
unnamed: D3.2 (A), R10.2
unnamed: D4.2 (A), R11.2
unnamed: D5.2 (A), R12.2
unnamed: D6.2 (A), R13.2
unnamed: D7.2 (A), R23.2
unnamed: Q1.2 (G1), R2.2
unnamed: Q1.4 (G2), R41.2
unnamed: Q2.2 (G1), R37.2
unnamed: Q2.4 (G2), R29.2
unnamed: U2.25 (VR_PA), U2.26 (BIAS_HP)
unnamed: R20.1, U5.11 (ADDR)
unnamed: C4.1, R20.2, U5.8 (DECAP)
unnamed: R32.1, U10.9 (ILM)
unnamed: C12.1, U10.10 (ITIMER)
unnamed: C18.1, U12.10 (CAP)
